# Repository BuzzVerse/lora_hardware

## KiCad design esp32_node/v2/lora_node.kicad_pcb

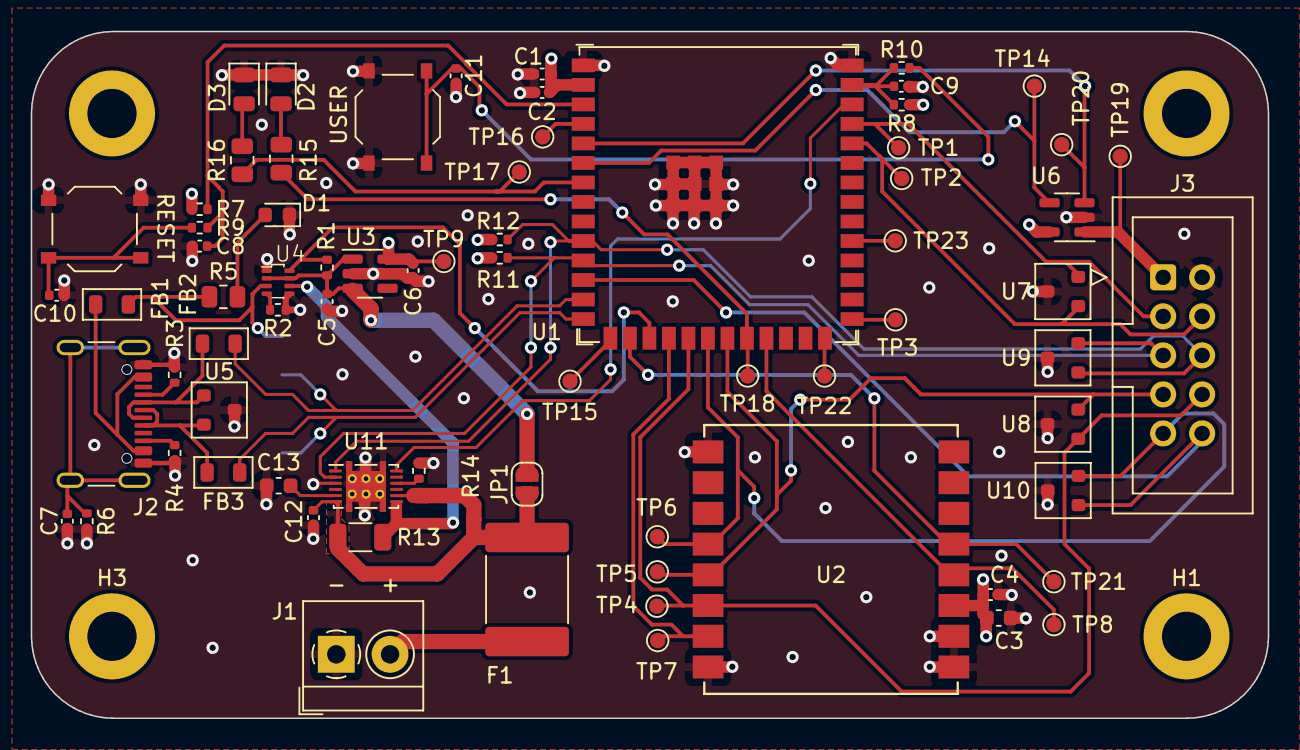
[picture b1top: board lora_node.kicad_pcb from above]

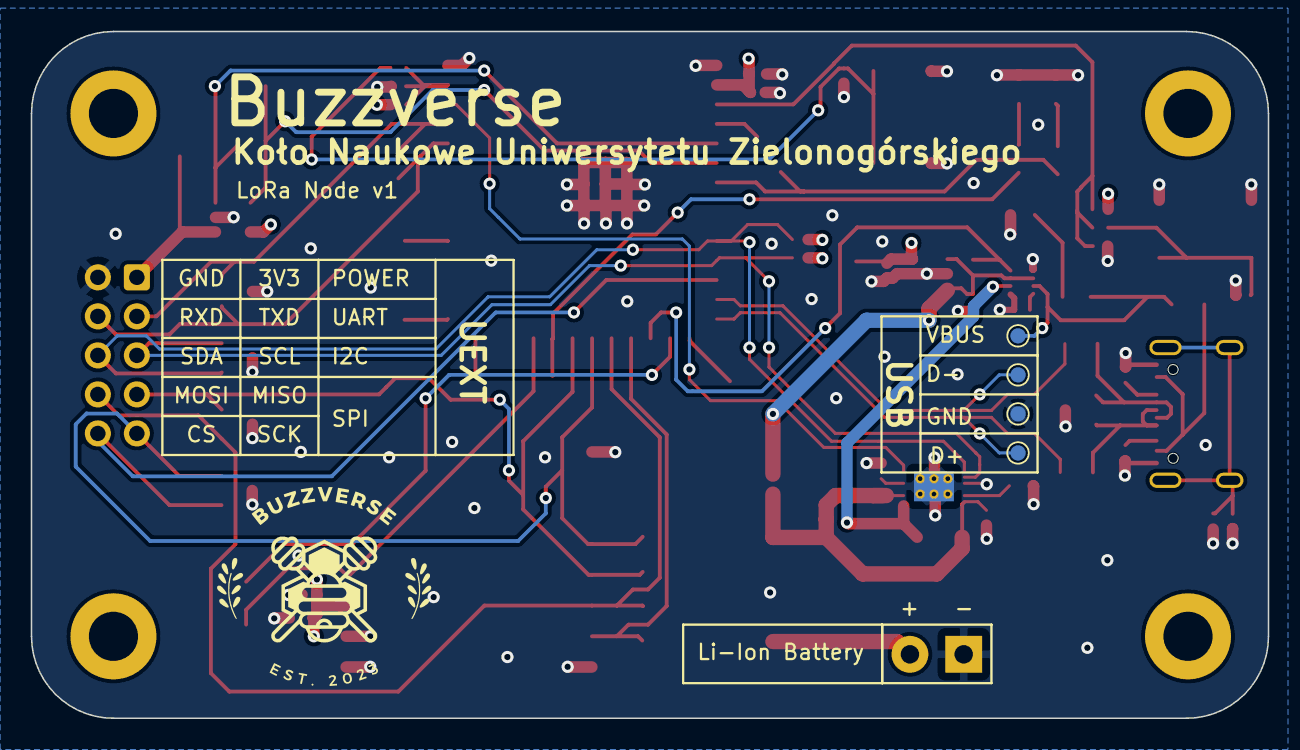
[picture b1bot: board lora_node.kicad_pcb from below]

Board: 4 copper layers, 80.5 x 44.7 mm, 80 parts (4 on the bottom side), 48 nets.

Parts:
C1: 10u; C_0402_1005Metric_Pad0.74x0.62mm_HandSolder
C2, C4, C10, C11: 100n; C_0402_1005Metric
C3: 22u; C_0603_1608Metric
C5, C6, C8, C9, C12: 1u; C_0402_1005Metric
C7: 15pF; C_0402_1005Metric
C13: 470n; C_0603_1608Metric
D1: RED LED; LED_0603_1608Metric
D2, D3: YELLOW LED; LED_0805_2012Metric
F1: Fuse; Fuse_2920_7451Metric
FB1, FB2, FB3: FerriteBead_Small; Ferrite_0805_2012Metric
H1, H2, H3, H4: MountingHole; MountingHole_3.2mm_M3_DIN965_Pad
J1: EXT_PWR; TerminalBlock_4Ucon_1x02_P3.50mm_Horizontal
J2: USB_C_Receptacle_USB2.0_16P; USB_C_Receptacle_GCT_USB4105-xx-A_16P_TopMnt_Horizontal
J3: Conn_02x05_Odd_Even; IDC-Header_2x05_P2.54mm_Vertical
JP1: SolderJumper_2_Open; SolderJumper-2_P1.3mm_Open_RoundedPad1.0x1.5mm
R1, R2, R7, R8, R14: 10k; R_0402_1005Metric
R3, R4: 5.1k; R_0402_1005Metric
R5, R15, R16: 4k7; R_0805_2012Metric
R6: 1M; R_0402_1005Metric
R9, R10: 1k; R_0402_1005Metric
R11, R12: 4k7; R_0402_1005Metric
R13: 10m; R_1206_3216Metric
SW1, SW2: SW_Push; SW_Push_1P1T_XKB_TS-1187A
TP1, TP2, TP3, TP4, TP5, TP6, TP7, TP8, TP9, TP10, TP11, TP12, TP13, TP14, TP15, TP16, TP17, TP18, TP19, TP20, TP21, TP22, TP23: TestPoint_Probe; TestPoint_Pad_D1.0mm
U1: ESP32-S3-WROOM-1; ESP32-S3-WROOM-1U
U2: Ai-Thinker-Ra-02; Ai-Thinker-Ra-01-LoRa
U3: MIC5504-3.3YM5; SOT-23-5
U4: LM66200; LM66200-SOT-5X3
U5, U7, U8, U9, U10: PSM712-LF-T7; SOT-23
U6: TPS2041B; SOT-23-5
U11: BQ27441DRZR-G1B; Texas_S-PDSO-N12

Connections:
+3V3: C1.1, C2.2, C3.1, C4.1, C6.1, R7.2, R8.2, R11.2, R12.2, TP9.1, U1.2 (3V3), U2.3 (VDD), U3.5 (VOUT), U6.5 (IN)
+BATT: C12.1, F1.1, JP1.1 (A), R13.1, U11.6 (BAT), U11.8 (SRP)
D+: FB3.2, TP12.1, U1.14 (GPIO20/U1CTS/ADC2_CH9/CLK_OUT1/USB_D+)
D-: FB2.1, TP11.1, U1.13 (GPIO19/U1RTS/ADC2_CH8/CLK_OUT2/USB_D-)
ENABLED: C8.1, R7.1, R9.2, U1.3 (EN)
GND: C1.2, C2.1, C3.2, C4.2, C5.2, C6.2, C7.1, C8.2, C9.2, C10.2, C11.2, C12.2, C13.2, D1.1 (K), D2.1 (K), D3.1 (K), J1.1, J2.A1 (GND), J2.A12 (GND), J2.B1 (GND), J2.B12 (GND), J3.2, R2.2, R3.2, R4.2, R6.1, R14.1, SW1.1, SW2.1, TP13.1, U1.1 (GND), U1.40 (GND), U1.41 (GND), U2.1 (GND), U2.2 (GND), U2.9 (GND), U2.16 (GND), U3.2 (GND), U4.1 (GND), U5.3 (A), U6.2 (GND), U7.3 (A), U8.3 (A), U9.3 (A), U10.3 (A), U11.3 (V_{SS}), U11.13 (PAD)
LORA_DIO0: TP21.1, U1.16 (GPIO46), U2.5 (DIO0)
LORA_MISO: J3.7, TP5.1, U1.21 (GPIO13/TOUCH13/ADC2_CH2/FSPIQ/FSPIIO7/S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), U2.13 (MISO), U8.2 (K2)
LORA_MOSI: J3.8, TP4.1, U1.19 (GPIO11/TOUCH11/ADC2_CH0/FSPID/FSPIIO5/S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), U2.14 (MOSI), U8.1 (K1)
LORA_NSS: TP7.1, U1.18 (GPIO10/TOUCH10/ADC1_CH9/FSPICS0/FSPIIO4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), U2.15 (~NSS)
LORA_RESET: TP8.1, U1.23 (GPIO21), U2.4 (~RESET)
LORA_SCK: J3.9, TP6.1, U1.20 (GPIO12/TOUCH12/ADC2_CH1/FSPICLK/FSPIIO6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), U2.12 (SCK), U10.2 (K2)
LOW_BATTERY: U1.38 (GPIO2/TOUCH2/ADC1_CH1), U11.12 (GPOUT)
unnamed: C10.1, R9.1, SW1.2
unnamed: C11.1, R10.1, SW2.2
unnamed: D1.2 (A), R5.2
unnamed: D2.2 (A), R15.2
unnamed: D3.2 (A), R16.2
unnamed: FB1.2, J2.A4 (VBUS), J2.A9 (VBUS), J2.B4 (VBUS), J2.B9 (VBUS)
unnamed: F1.2, J1.2
unnamed: J2.A5 (CC1), R3.1
unnamed: J2.B5 (CC2), R4.1
unnamed: C7.2, J2.S1 (SHIELD), R6.2
unnamed: J3.1, TP19.1, U6.1 (OUT)
unnamed: C5.1, JP1.2 (B), R1.1, U3.1 (VIN), U3.3 (EN), U4.2 (VOUT)
unnamed: TP3.1, U1.27 (GPIO0/BOOT)
unnamed: TP15.1, U1.15 (GPIO3/TOUCH3/ADC1_CH2)
unnamed: TP16.1, U1.4 (GPIO4/TOUCH4/ADC1_CH3)
unnamed: R16.1, TP17.1, U1.7 (GPIO7/TOUCH7/ADC1_CH6)
unnamed: R15.1, TP18.1, U1.22 (GPIO14/TOUCH14/ADC2_CH3/FSPIWP/FSPIDQS/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)
unnamed: TP23.1, U1.31 (GPIO38/FSPIWP/SUBSPIWP)
unnamed: TP22.1, U1.26 (GPIO45)
unnamed: R2.1, U4.4 (~EN)
unnamed: FB2.2, J2.A7 (D-), J2.B7 (D-), U5.1 (K1)
unnamed: FB3.1, J2.A6 (D+), J2.B6 (D+), U5.2 (K2)
unnamed: R14.2, U11.10 (BIN)
unnamed: C13.1, U11.5 (V_{DD})
PERIPHERAL_ENABLED: TP14.1, U1.6 (GPIO6/TOUCH6/ADC1_CH5), U6.4 (~EN)
PERIPHERAL_OVERCURRENT: TP20.1, U1.5 (GPIO5/TOUCH5/ADC1_CH4), U6.3 (~OC)
SUPP_SRC_INDICATOR: R1.2, U1.17 (GPIO9/TOUCH9/ADC1_CH8/FSPIHD/SUBSPIHD), U4.8 (ST)
UEXT_RXD: J3.4, TP2.1, U1.36 (U0RXD/GPIO44/CLK_OUT2), U7.1 (K1)
UEXT_SCL: J3.5, R11.1, U1.11 (GPIO18/U1RXD/ADC2_CH7/CLK_OUT3), U9.2 (K2), U11.2 (SCL)
UEXT_SDA: J3.6, R12.1, U1.10 (GPIO17/U1TXD/ADC2_CH6), U9.1 (K1), U11.1 (SDA)
UEXT_SSEL: J3.10, U1.12 (GPIO8/TOUCH8/ADC1_CH7/SUBSPICS1), U10.1 (K1)
UEXT_TXD: J3.3, TP1.1, U1.37 (U0TXD/GPIO43/CLK_OUT1), U7.2 (K2)
USER_BUTTON: C9.1, R8.1, R10.2, U1.39 (GPIO1/TOUCH1/ADC1_CH0)
VBUS: FB1.1, R5.1, TP10.1, U4.3 (VIN1)
VSYS: R13.2, U4.6 (VIN2), U11.7 (SRN)
